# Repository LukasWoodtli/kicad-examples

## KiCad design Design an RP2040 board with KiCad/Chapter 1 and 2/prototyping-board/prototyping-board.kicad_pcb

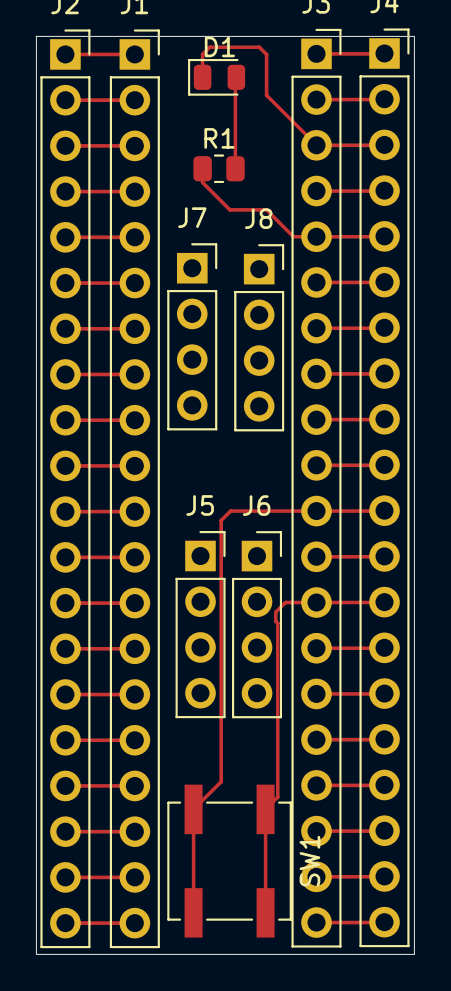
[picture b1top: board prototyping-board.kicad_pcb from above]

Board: 2 copper layers, 21.0 x 51.0 mm, 11 parts (0 on the bottom side), 41 nets.

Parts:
D1: LED; LED_0805_2012Metric
J1: Left Breakout; PinSocket_1x20_P2.54mm_Vertical
J2: Left Pico; PinSocket_1x20_P2.54mm_Vertical
J3: Right Pico; PinSocket_1x20_P2.54mm_Vertical
J4: Right Breakout; PinSocket_1x20_P2.54mm_Vertical
J5, J6, J7, J8: Conn_01x04_Pin; PinSocket_1x04_P2.54mm_Vertical
R1: R; R_0805_2012Metric
SW1: SW_SPST; SW_SPST_B3SL-1002P

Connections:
unnamed: D1.2 (A), R1.2
unnamed: D1.1 (K), J3.3, J4.3
unnamed: J1.1, J2.1
unnamed: J1.2, J2.2
unnamed: J1.3, J2.3
unnamed: J1.4, J2.4
unnamed: J1.5, J2.5
unnamed: J1.6, J2.6
unnamed: J1.7, J2.7
unnamed: J1.8, J2.8
unnamed: J1.9, J2.9
unnamed: J1.10, J2.10
unnamed: J1.11, J2.11
unnamed: J1.12, J2.12
unnamed: J1.13, J2.13
unnamed: J1.14, J2.14
unnamed: J1.15, J2.15
unnamed: J1.16, J2.16
unnamed: J1.17, J2.17
unnamed: J1.18, J2.18
unnamed: J1.19, J2.19
unnamed: J1.20, J2.20
unnamed: J3.1, J4.1
unnamed: J3.2, J4.2
unnamed: J3.4, J4.4
unnamed: J3.5, J4.5, R1.1
unnamed: J3.6, J4.6
unnamed: J3.7, J4.7
unnamed: J3.8, J4.8
unnamed: J3.9, J4.9
unnamed: J3.10, J4.10
unnamed: J3.11, J4.11, SW1.2 (B)
unnamed: J3.12, J4.12
unnamed: J3.13, J4.13, SW1.1 (A)
unnamed: J3.14, J4.14
unnamed: J3.15, J4.15
unnamed: J3.16, J4.16
unnamed: J3.17, J4.17
unnamed: J3.18, J4.18
unnamed: J3.19, J4.19
unnamed: J3.20, J4.20

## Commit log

2025-10-06 Add first schematic for prototyping board
2025-10-14 Add layout for prototyping board
2025-10-14 Add files from official book repo
2025-11-27 Add documentation and supporting files for RP2040
    These are official docs.
2025-11-27 Add schematics for RP2040 example
2025-12-04 Small improvements for RP2040 board
2025-12-04 Add documentation for RP2350
2025-12-05 Work on RP2354a board
2025-12-11 Finish schematic for RP235xA board
2025-12-11 Rename project
2025-12-11 Some fixes in schematic
2025-12-11 Finish assignment of footprints
2026-01-18 Libraries, Symbols and Footprint
